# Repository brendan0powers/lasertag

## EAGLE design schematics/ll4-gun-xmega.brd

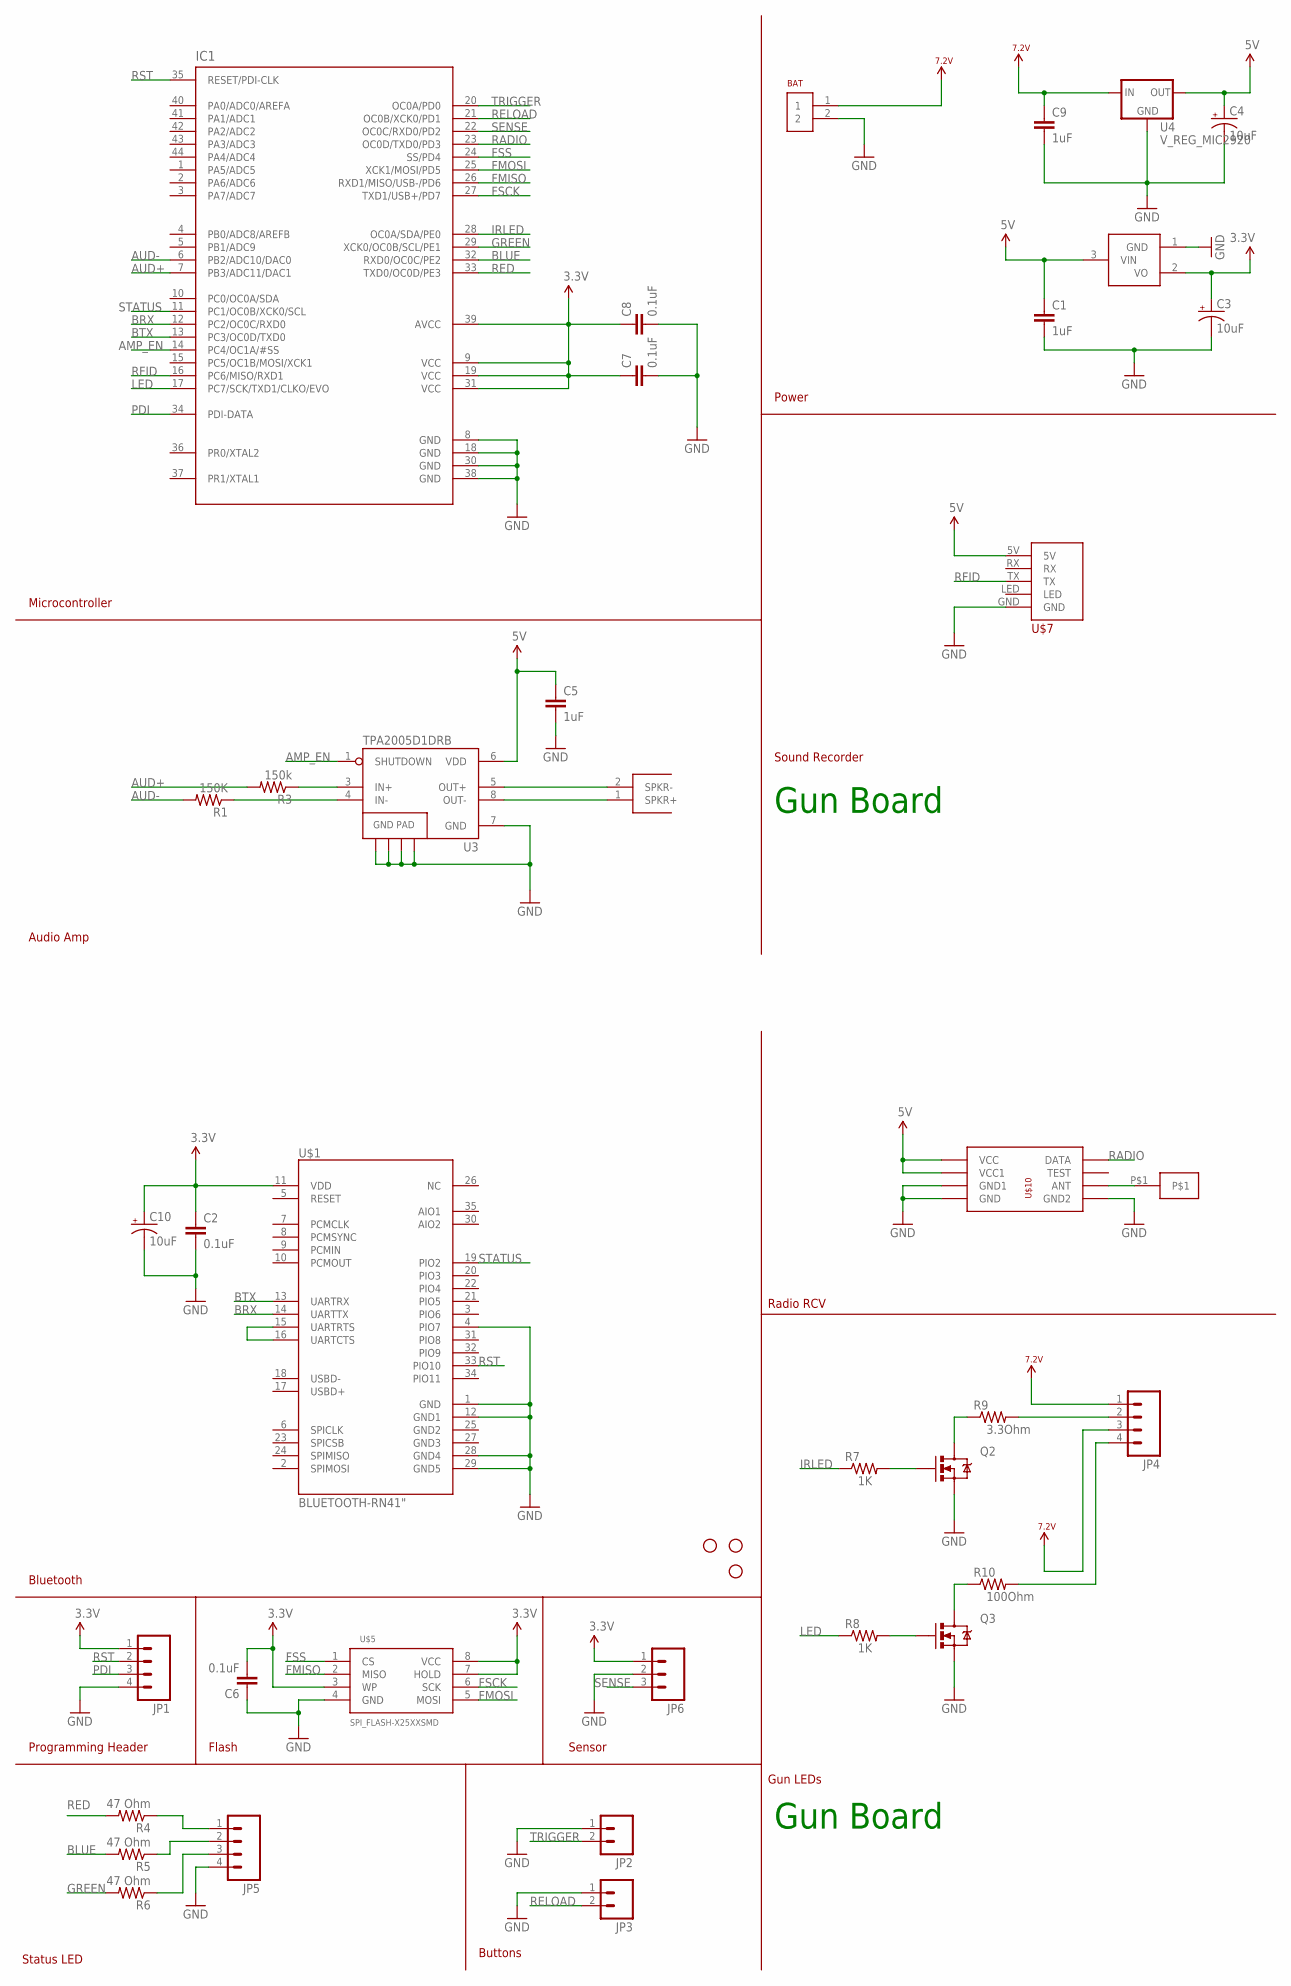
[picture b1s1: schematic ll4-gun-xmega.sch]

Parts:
BAT: 2HEAD
C1, C5, C9: 1uF; C0603
C2, C6, C7, C8: 0.1uF; C0603
C3, C4, C10: 10uF; EIA3216
IC1: ATXMEGAXXA4U; TQFP-44
JP1, JP4, JP5: M04JST-PTH; JST-4-PTH
JP2, JP3: M02JST-PTH-2; JST-2-PTH
JP6: M03JST-PTH; JST-3-PTH
JP7, JP9, JP10: STAND-OFF
Q2, Q3: MOSFET-NCHANNELSMD; SOT23-3
R1: 150K; R0603
R3: 150k; R0603
R4, R5, R6: 47 Ohm; 0805
R7, R8: 1K; 0805
R9: 3.3Ohm; AXIAL-0.5
R10: 100Ohm; AXIAL-0.5
SPEAKER: SPKRHEAD
U2: VREG; SOT23-3
U3: TPA2005D1DRB; QFN-8_PAD
U4: V_REG_MIC2920; SOT223
U$1: BLUETOOTH-RN41"; RN41
U$5: SPI_FLASH-X25XXSMD; SO08
U$7: RFID
U$10: RFLINK-RCV
U$12: 1HEAD

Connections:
3.3V: C2.1, C3.A (+), C6.2, C7.1, C8.1, C10.A (+), IC1.9 (VCC), IC1.19 (VCC), IC1.31 (VCC), IC1.39 (AVCC), JP1.1, JP6.1, U2.2 (VO), U$1.11 (VDD), U$5.3 (WP), U$5.7 (HOLD), U$5.8 (VCC)
5V: C1.1, C4.A (+), C5.1, U2.3 (VIN), U3.6 (VDD), U4.3 (OUT), U$7.5V, U$10.VCC (VCC1), U$10.VCC1 (VCC)
7.2V: BAT.1, C9.1, JP4.1, JP4.3, U4.1 (IN)
AMP_EN: IC1.14 (PC4/OC1A/#SS), U3.1 (SHUTDOWN)
AUD+: IC1.7 (PB3/ADC11/DAC1), R3.2
AUD-: IC1.6 (PB2/ADC10/DAC0), R1.2
BLUE: IC1.32 (RXD0/OC0C/PE2), R5.2
BRX: IC1.12 (PC2/OC0C/RXD0), U$1.14 (UARTTX)
BTX: IC1.13 (PC3/OC0D/TXD0), U$1.13 (UARTRX)
FMISO: IC1.26 (RXD1/MISO/USB-/PD6), U$5.2 (MISO)
FMOSI: IC1.25 (XCK1/MOSI/PD5), U$5.5 (MOSI)
FSCK: IC1.27 (TXD1/USB+/PD7), U$5.6 (SCK)
FSS: IC1.24 (SS/PD4), U$5.1 (CS)
GND: BAT.2, C1.2, C2.2, C3.C (-), C4.C (-), C5.2, C6.1, C7.2, C8.2, C9.2, C10.C (-), IC1.8 (GND), IC1.18 (GND), IC1.30 (GND), IC1.38 (GND), JP1.4, JP2.1, JP3.1, JP5.4, JP6.2, Q2.2 (S), Q3.2 (S), U2.1 (GND), U3.7 (GND), U3.10 (GND), U3.11 (GND), U3.12 (GND), U3.13 (GND), U4.2 (GND), U$1.1 (GND), U$1.4 (PIO7), U$1.12 (GND1), U$1.28 (GND4), U$1.29 (GND5), U$5.4 (GND), U$7.GND, U$10.GND (GND1), U$10.GND1 (GND2), U$10.GND2 (GND)
GREEN: IC1.29 (XCK0/OC0B/SCL/PE1), R6.2
IRLED: IC1.28 (OC0A/SDA/PE0), R7.1
LED: IC1.17 (PC7/SCK/TXD1/CLKO/EVO), R8.1
LINK: U$1.15 (UARTRTS), U$1.16 (UARTCTS)
unnamed: SPEAKER.2 (SPKR-), U3.5 (OUT+)
unnamed: SPEAKER.1 (SPKR+), U3.8 (OUT-)
unnamed: R3.1, U3.3 (IN+)
unnamed: R1.1, U3.4 (IN-)
unnamed: U$10.ANT, U$12.P$1
unnamed: JP4.2, R9.P$2 (2)
unnamed: JP4.4, R10.P$2 (2)
unnamed: JP5.1, R4.1
unnamed: JP5.2, R5.1
unnamed: JP5.3, R6.1
unnamed: Q2.1 (G), R7.2
unnamed: Q3.1 (G), R8.2
unnamed: Q3.3 (D), R10.P$1 (1)
unnamed: Q2.3 (D), R9.P$1 (1)
PDI: IC1.34 (PDI-DATA), JP1.3
RADIO: IC1.23 (OC0D/TXD0/PD3), U$10.DATA
RED: IC1.33 (TXD0/OC0D/PE3), R4.2
RELOAD: IC1.21 (OC0B/XCK0/PD1), JP3.2
RFID: IC1.16 (PC6/MISO/RXD1), U$7.TX
RST: IC1.35 (RESET/PDI-CLK), JP1.2, U$1.33 (PIO10)
SENSE: IC1.22 (OC0C/RXD0/PD2), JP6.3
STATUS: IC1.11 (PC1/OC0B/XCK0/SCL), U$1.19 (PIO2)
TRIGGER: IC1.20 (OC0A/PD0), JP2.2

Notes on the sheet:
Gun Board
Microcontroller
Audio Amp
Sound Recorder
Power
Radio RCV
Gun LEDs
Status LED
Buttons
Bluetooth
Sensor
Programming Header
Flash

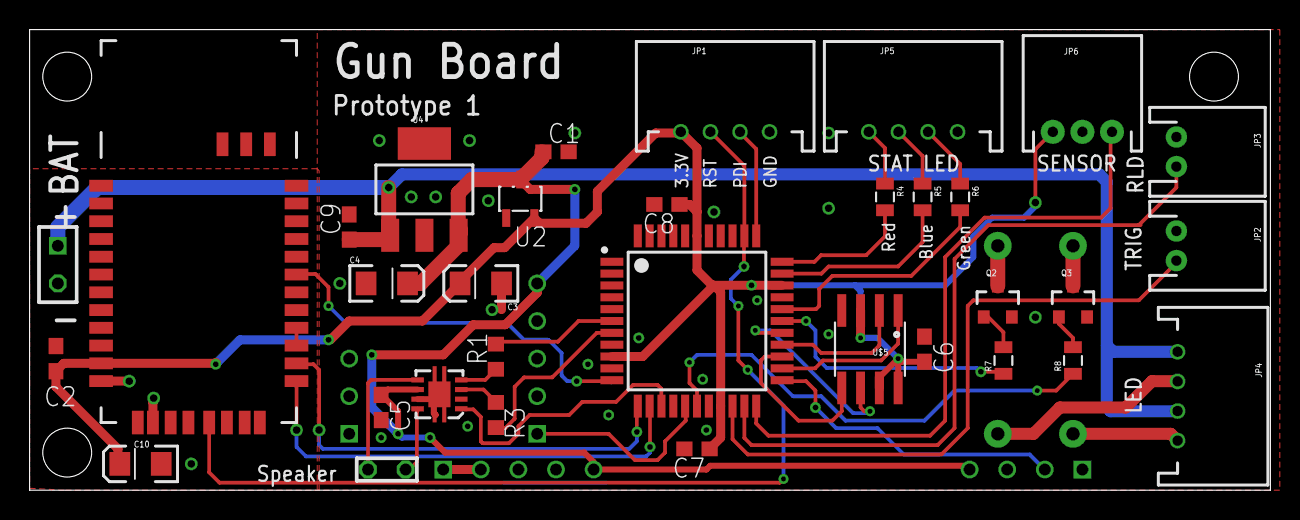
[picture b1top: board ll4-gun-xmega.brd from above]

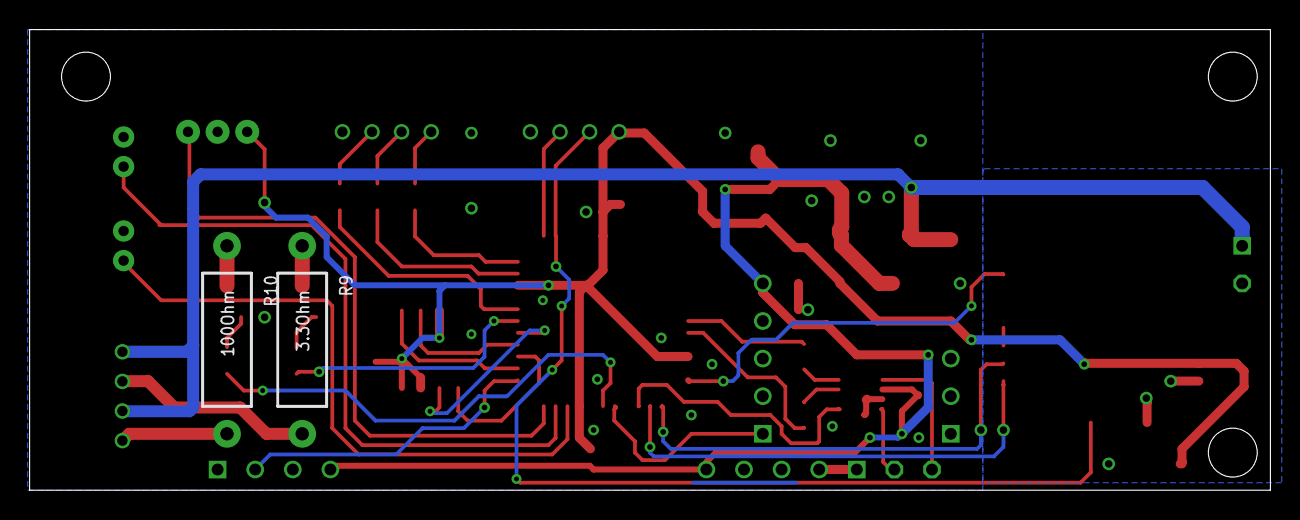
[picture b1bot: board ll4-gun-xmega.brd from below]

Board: 2 copper layers, 83.8 x 31.1 mm, 41 parts (3 on the bottom side), 41 nets.
